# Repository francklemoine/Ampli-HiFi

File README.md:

# HiFi

This repository contains my amplifier and pre-amplifier schematics, program and housing.

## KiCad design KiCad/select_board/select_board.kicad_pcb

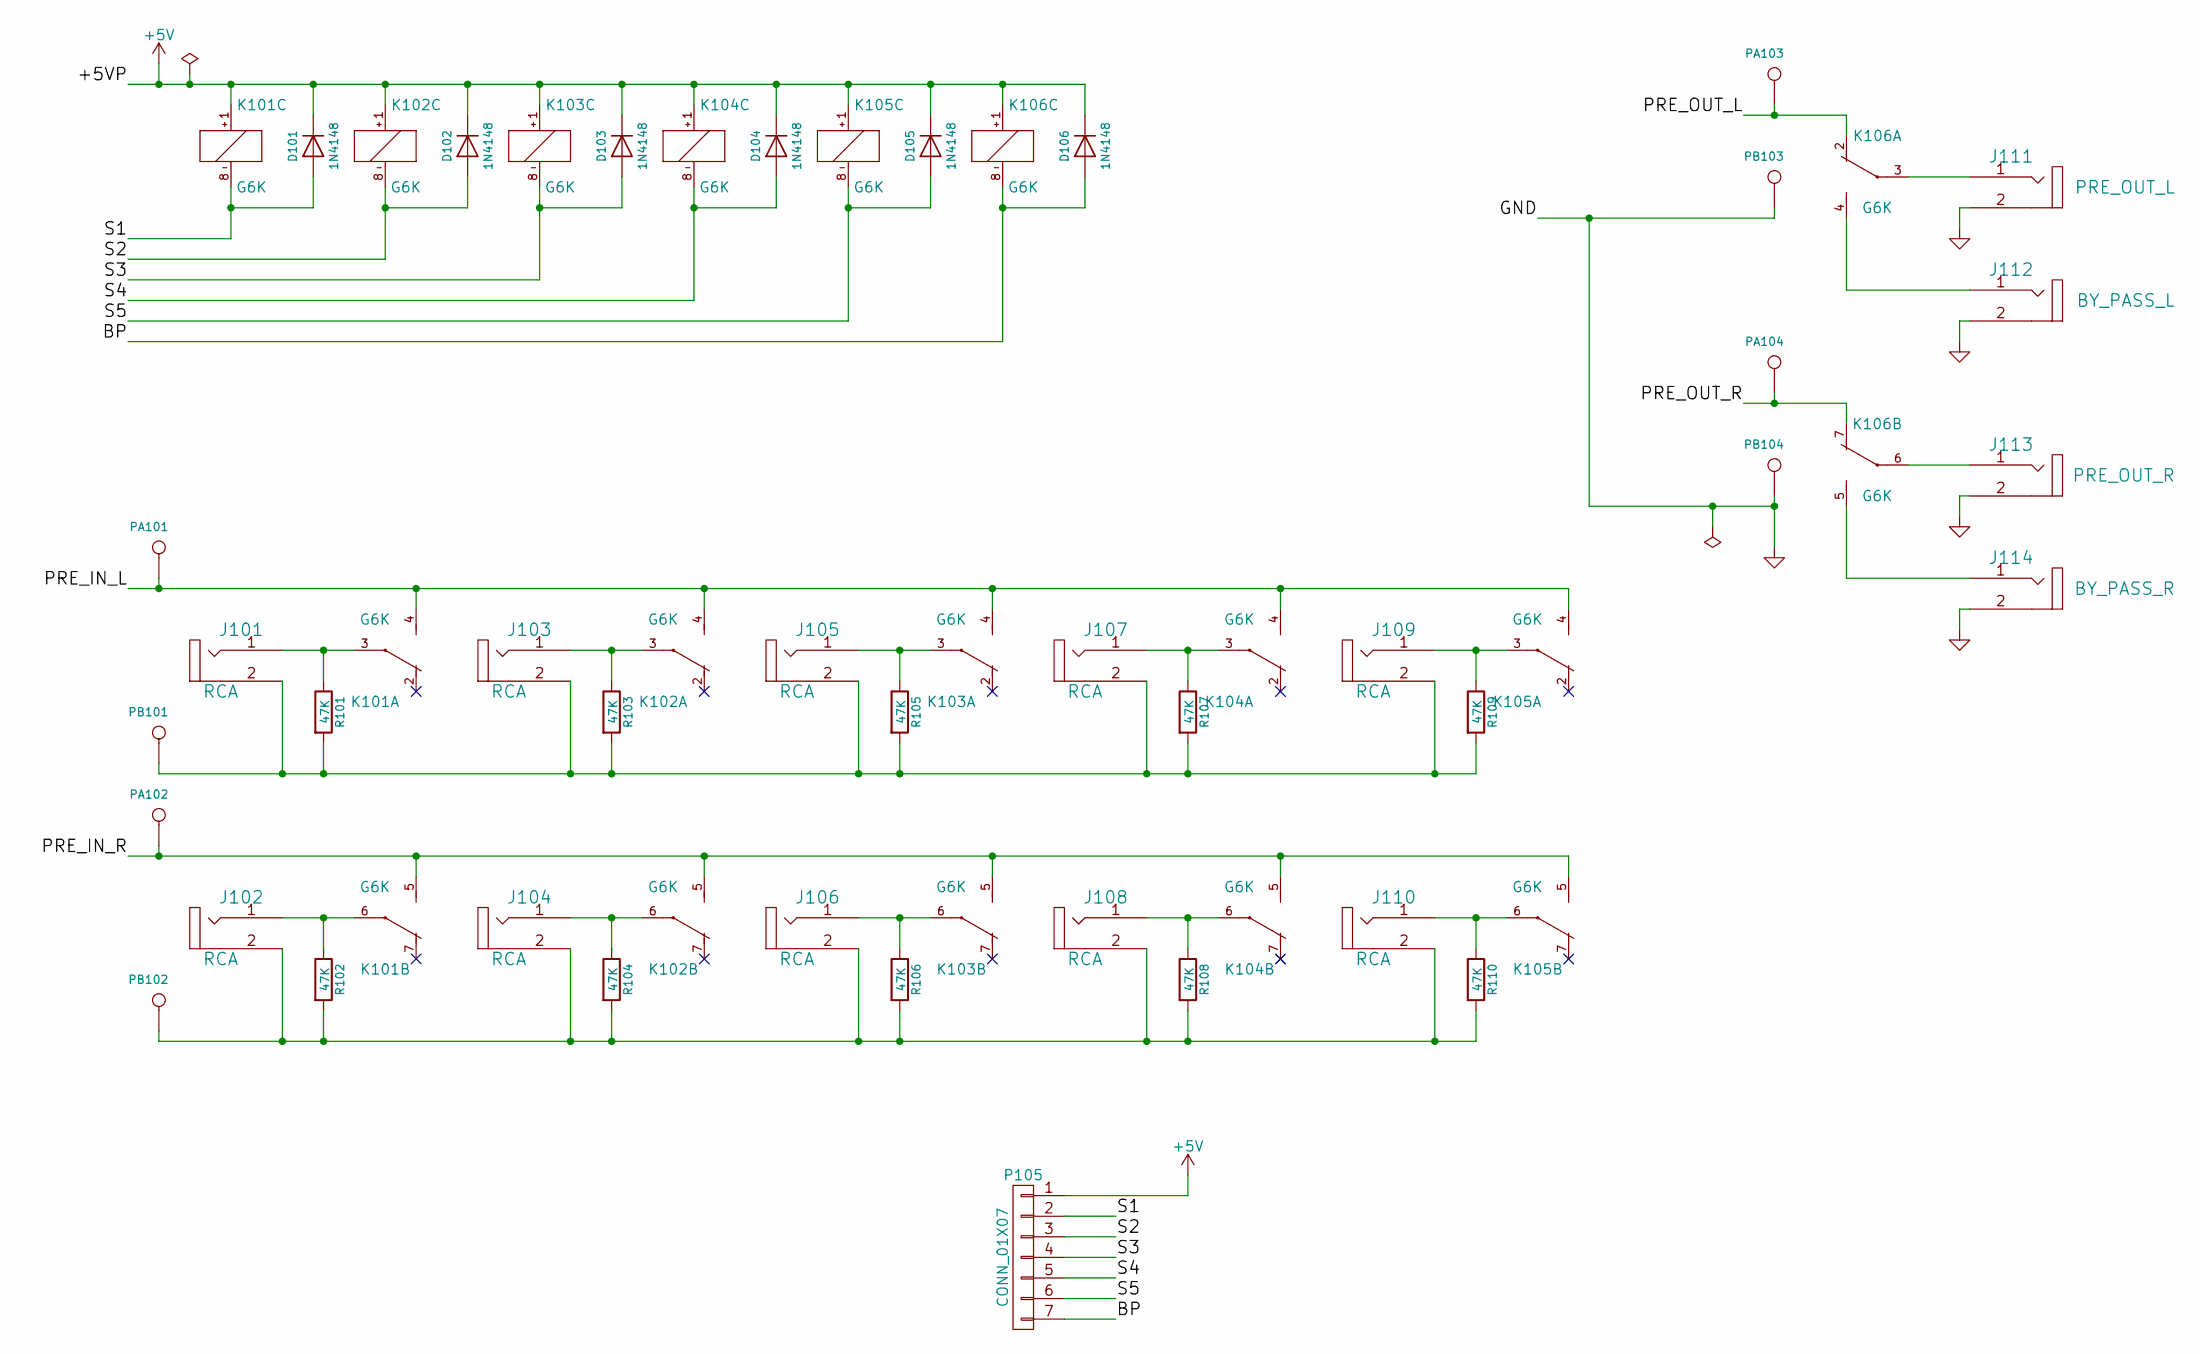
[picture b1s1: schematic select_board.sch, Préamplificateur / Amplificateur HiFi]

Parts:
D101, D102, D103, D104, D105, D106: 1N4148; D_DO-35_SOD27_P7.62mm_Horizontal
J101, J102, J103, J104, J105, J106, J107, J108, J109, J110: RCA; RCA_ELECAUDIO_ER107
J111: PRE_OUT_L; RCA_ELECAUDIO_ER107
J112: BY_PASS_L; RCA_ELECAUDIO_ER107
J113: PRE_OUT_R; RCA_ELECAUDIO_ER107
J114: BY_PASS_R; RCA_ELECAUDIO_ER107
K101, K102, K103, K104, K105, K106: G6K; Omron-G6K-2F-Y
P105: CONN_01X07; Pin_Header_Straight_1x07_Pitch2.54mm
PA101, PA102, PA103, PA104: CONN_1; 1Pin_d1.8mm_D3.4mm
PB101, PB102, PB103, PB104: CONN_1; 1Pin_d1.8mm_D3.4mm
R101, R102, R103, R104, R105, R106, R107, R108, R109, R110: 47K; R_1206

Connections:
+5V: D101.1 (K), D102.1 (K), D103.1 (K), D104.1 (K), D105.1 (K), D106.1 (K), K101.1 (+), K102.1 (+), K103.1 (+), K104.1 (+), K105.1 (+), K106.1 (+), P105.1
/BP: D106.2 (A), K106.8 (-), P105.7
/PRE_IN_L: K101.4 (S), K102.4 (S), K103.4 (S), K104.4 (S), K105.4 (S), PA101.1
/PRE_IN_R: K101.5 (S), K102.5 (S), K103.5 (S), K104.5 (S), K105.5 (S), PA102.1
/PRE_OUT_L: K106.2 (O), PA103.1
/PRE_OUT_R: K106.7 (O), PA104.1
/S1: D101.2 (A), K101.8 (-), P105.2
/S2: D102.2 (A), K102.8 (-), P105.3
/S3: D103.2 (A), K103.8 (-), P105.4
/S4: D104.2 (A), K104.8 (-), P105.5
/S5: D105.2 (A), K105.8 (-), P105.6
GND: J111.2 (S), J112.2 (S), J113.2 (S), J114.2 (S), PB103.1, PB104.1
unnamed: J101.1 (T), K101.3, R101.1
unnamed: J101.2 (S), J103.2 (S), J105.2 (S), J107.2 (S), J109.2 (S), PB101.1, R101.2, R103.2, R105.2, R107.2, R109.2
unnamed: J102.1 (T), K101.6, R102.1
unnamed: J102.2 (S), J104.2 (S), J106.2 (S), J108.2 (S), J110.2 (S), PB102.1, R102.2, R104.2, R106.2, R108.2, R110.2
unnamed: J103.1 (T), K102.3, R103.1
unnamed: J104.1 (T), K102.6, R104.1
unnamed: J105.1 (T), K103.3, R105.1
unnamed: J106.1 (T), K103.6, R106.1
unnamed: J107.1 (T), K104.3, R107.1
unnamed: J108.1 (T), K104.6, R108.1
unnamed: J109.1 (T), K105.3, R109.1
unnamed: J110.1 (T), K105.6, R110.1
unnamed: J111.1 (T), K106.3
unnamed: J112.1 (T), K106.4 (S)
unnamed: J113.1 (T), K106.6
unnamed: J114.1 (T), K106.5 (S)

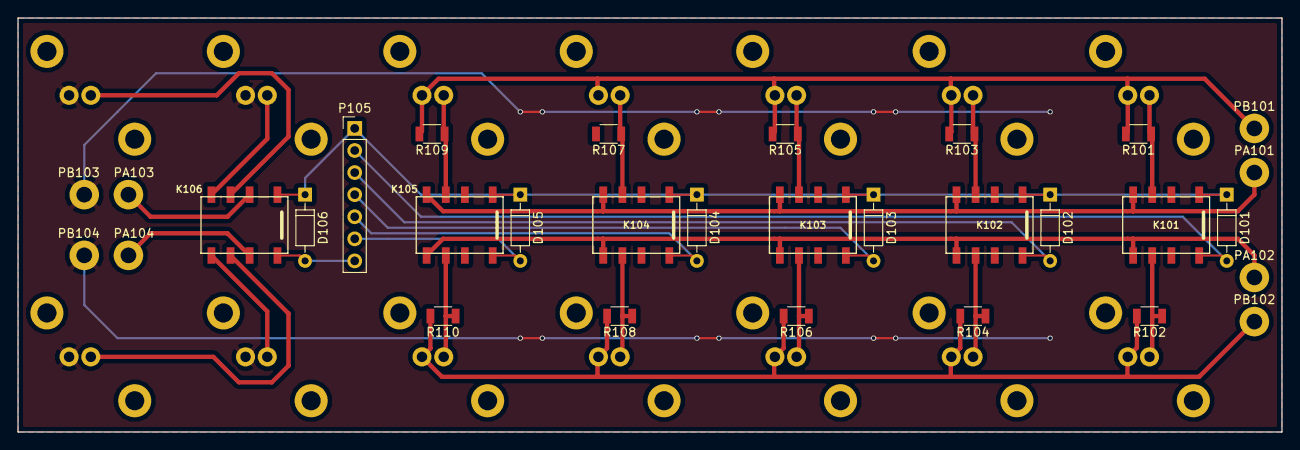
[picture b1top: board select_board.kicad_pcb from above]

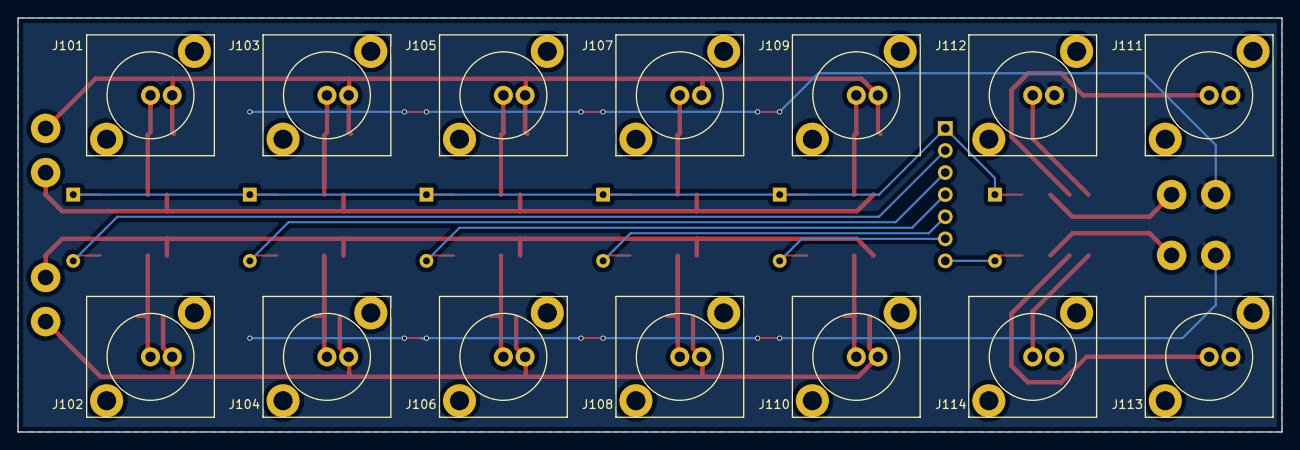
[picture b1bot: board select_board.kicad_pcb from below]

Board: 2 copper layers, 145.4 x 47.6 mm, 45 parts (14 on the bottom side), 28 nets.

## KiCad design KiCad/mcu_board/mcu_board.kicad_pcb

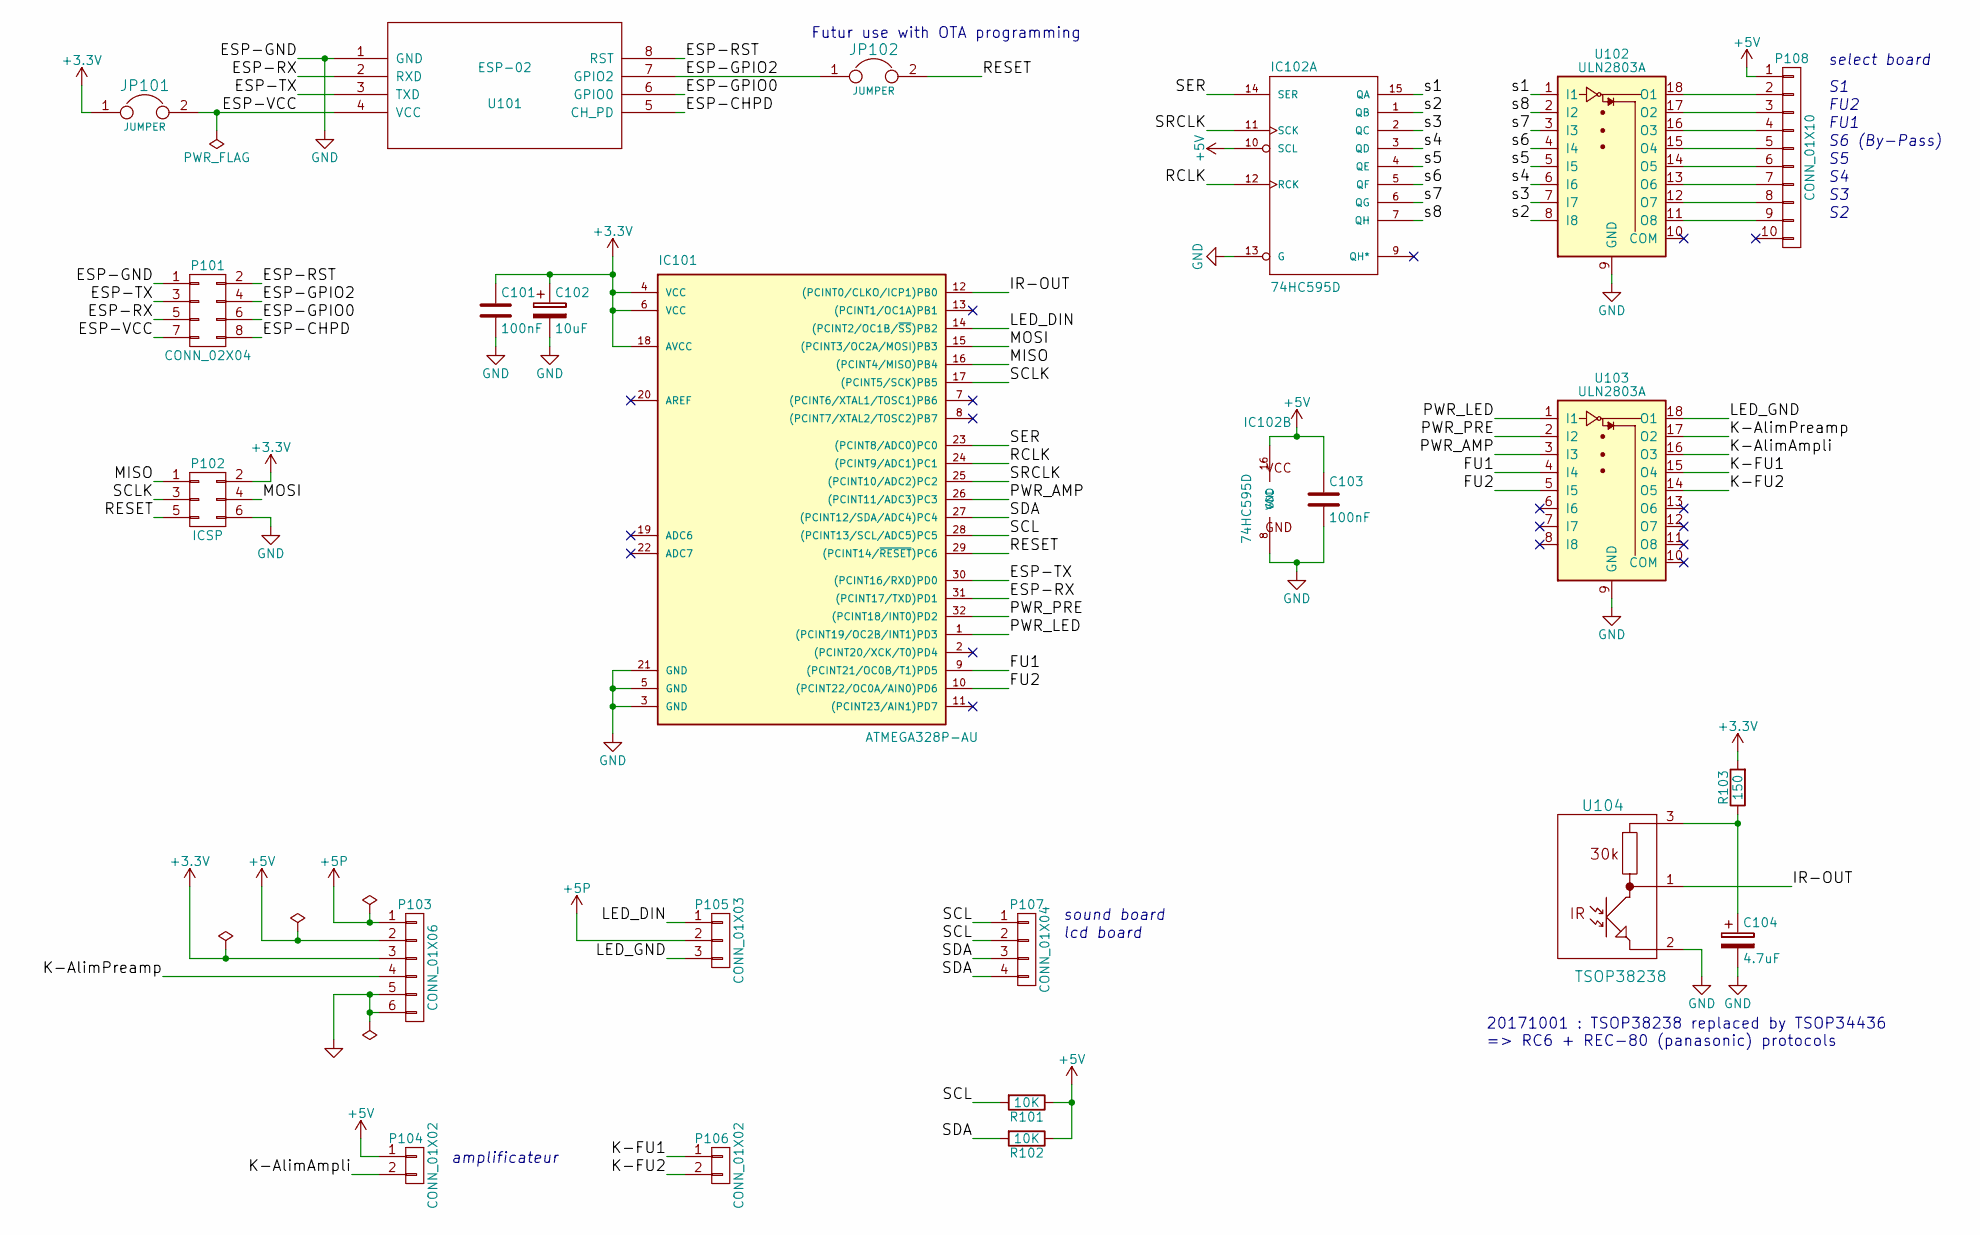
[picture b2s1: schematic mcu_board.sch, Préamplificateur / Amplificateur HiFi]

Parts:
C101, C103: 100nF; C_0603_HandSoldering
C102: 10uF; CP_Radial_D5.0mm_P2.50mm
C104: 4.7uF; CP_Radial_D5.0mm_P2.50mm
IC101: ATMEGA328P-AU; TQFP-32_7x7mm_Pitch0.8mm
IC102: 74HC595D; SO-16-N
JP101, JP102: JUMPER; Test_Point_2Pads
P101: CONN_02X04; Pin_Header_Straight_2x04_Pitch2.54mm
P102: ICSP; Pin_Header_Straight_2x03_Pitch2.54mm
P103: CONN_01X06; Pin_Header_Straight_1x06_Pitch2.54mm
P104, P106: CONN_01X02; Pin_Header_Straight_1x02_Pitch2.54mm
P105: CONN_01X03; Pin_Header_Straight_1x03_Pitch2.54mm
P107: CONN_01X04; Pin_Header_Straight_1x04_Pitch2.54mm
P108: CONN_01X10; Pin_Header_Straight_1x10_Pitch2.54mm
R101, R102: 10K; R_1206_HandSoldering
R103: 150; R_1206_HandSoldering
U101: ESP-02; ESP8266_ESP_02_SMD_Handsoldering
U102, U103: ULN2803A; SOIC-18W_7.5x11.6mm_Pitch1.27mm
U104: TSOP38238; TSOP382

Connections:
+3V3: C101.1, C102.1, IC101.4 (VCC), IC101.6 (VCC), IC101.18 (AVCC), JP101.1, P102.2, P103.3, R103.2
+5P: P103.1, P105.2
+5V: C103.1, IC102.10 (SCL), IC102.16 (VCC), P103.2, P104.1, P108.1, R101.1, R102.1
/ESP-CHPD: P101.8, U101.5 (CH_PD)
/ESP-GPIO0: P101.6, U101.6 (GPIO0)
/ESP-GPIO2: JP102.1, P101.4, U101.7 (GPIO2)
/ESP-RST: P101.2, U101.8 (RST)
/ESP-RX: IC101.31 ((PCINT17/TXD)PD1), P101.5, U101.2 (RXD)
/ESP-TX: IC101.30 ((PCINT16/RXD)PD0), P101.3, U101.3 (TXD)
/ESP-VCC: JP101.2, P101.7, U101.4 (VCC)
/FU1: IC101.9 ((PCINT21/OC0B/T1)PD5), U103.4 (I4)
/FU2: IC101.10 ((PCINT22/OC0A/AIN0)PD6), U103.5 (I5)
/IR-OUT: IC101.12 ((PCINT0/CLKO/ICP1)PB0), U104.1
/K-AlimAmpli: P104.2, U103.16 (O3)
/K-AlimPreamp: P103.4, U103.17 (O2)
/K-FU1: P106.1, U103.15 (O4)
/K-FU2: P106.2, U103.14 (O5)
/LED_DIN: IC101.14 ((PCINT2/OC1B/~SS~)PB2), P105.1
/LED_GND: P105.3, U103.18 (O1)
/MISO: IC101.16 ((PCINT4/MISO)PB4), P102.1
/MOSI: IC101.15 ((PCINT3/OC2A/MOSI)PB3), P102.4
/PWR_AMP: IC101.26 ((PCINT11/ADC3)PC3), U103.3 (I3)
/PWR_LED: IC101.1 ((PCINT19/OC2B/INT1)PD3), U103.1 (I1)
/PWR_PRE: IC101.32 ((PCINT18/INT0)PD2), U103.2 (I2)
/RCLK: IC101.24 ((PCINT9/ADC1)PC1), IC102.12 (RCK)
/RESET: IC101.29 ((PCINT14/~RESET~)PC6), JP102.2, P102.5
/SCL: IC101.28 ((PCINT13/SCL/ADC5)PC5), P107.1, P107.2, R101.2
/SCLK: IC101.17 ((PCINT5/SCK)PB5), P102.3
/SDA: IC101.27 ((PCINT12/SDA/ADC4)PC4), P107.3, P107.4, R102.2
/SER: IC101.23 ((PCINT8/ADC0)PC0), IC102.14 (SER)
/SRCLK: IC101.25 ((PCINT10/ADC2)PC2), IC102.11 (SCK)
/s1: IC102.15 (QA), U102.1 (I1)
/s2: IC102.1 (QB), U102.8 (I8)
/s3: IC102.2 (QC), U102.7 (I7)
/s4: IC102.3 (QD), U102.6 (I6)
/s5: IC102.4 (QE), U102.5 (I5)
/s6: IC102.5 (QF), U102.4 (I4)
/s7: IC102.6 (QG), U102.3 (I3)
/s8: IC102.7 (QH), U102.2 (I2)
GND: C101.2, C102.2, C103.2, C104.2, IC101.3 (GND), IC101.5 (GND), IC101.21 (GND), IC102.8 (GND), IC102.13 (G), P101.1, P102.6, P103.5, P103.6, U101.1 (GND), U102.9 (GND), U103.9 (GND), U104.2
unnamed: C104.1, R103.1, U104.3
unnamed: P108.2, U102.18 (O1)
unnamed: P108.3, U102.17 (O2)
unnamed: P108.4, U102.16 (O3)
unnamed: P108.5, U102.15 (O4)
unnamed: P108.6, U102.14 (O5)
unnamed: P108.7, U102.13 (O6)
unnamed: P108.8, U102.12 (O7)
unnamed: P108.9, U102.11 (O8)

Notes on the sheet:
select board
amplificateur
sound board
lcd board
S6 (By-Pass)
FU1
FU2
Futur use with OTA programming
20171001 : TSOP38238 replaced by TSOP34436 => RC6 + REC-80 (panasonic) protocols

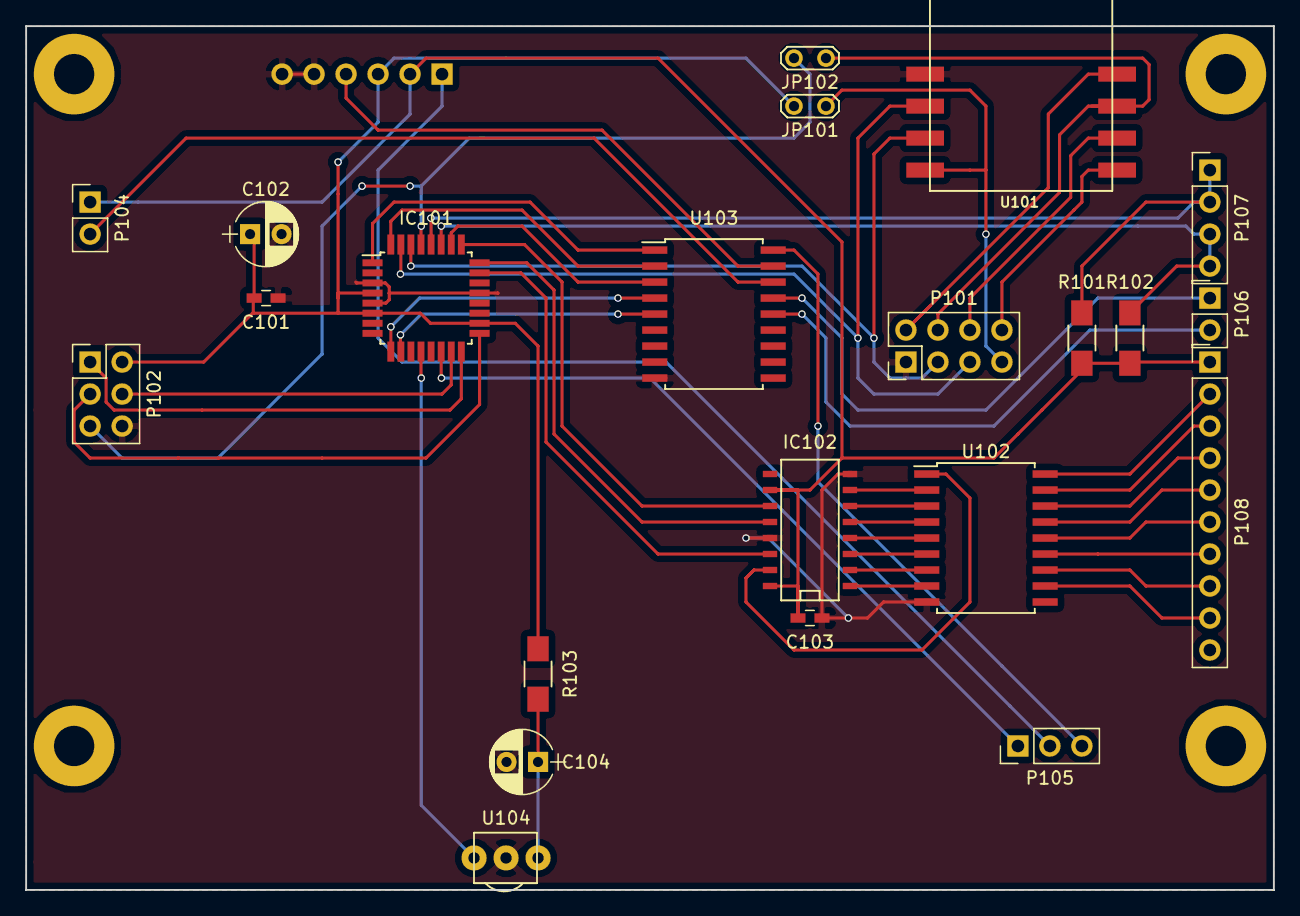
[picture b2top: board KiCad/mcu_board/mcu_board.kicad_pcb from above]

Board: 2 copper layers, 99.1 x 68.6 mm, 23 parts (1 on the bottom side), 49 nets.

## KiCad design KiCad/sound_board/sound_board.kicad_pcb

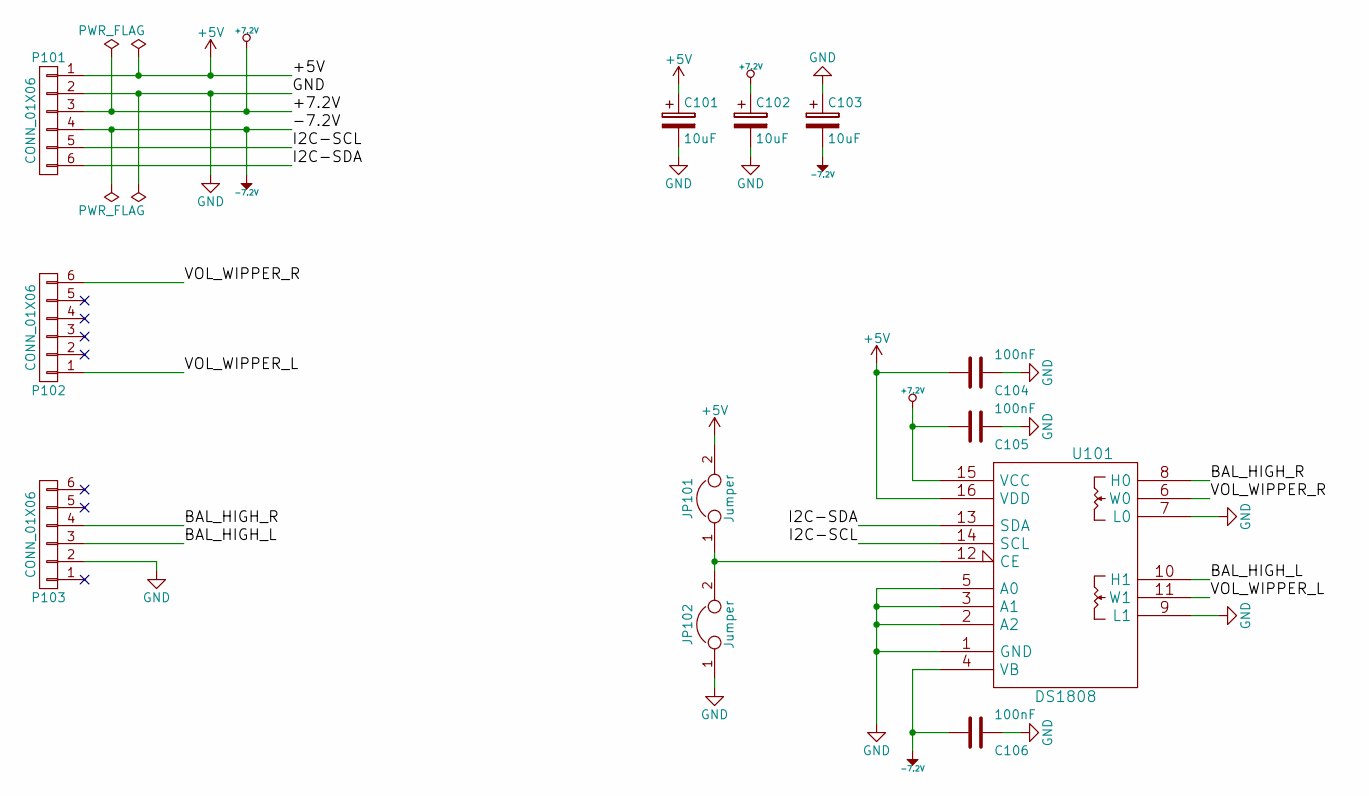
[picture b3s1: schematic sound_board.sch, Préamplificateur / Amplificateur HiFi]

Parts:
C101, C102, C103: 10uF; CP_Radial_D5.0mm_P2.50mm
C104, C105, C106: 100nF; C_0603_HandSoldering
JP101, JP102: Jumper; Test_Point_2Pads
P101, P102, P103: CONN_01X06; Pin_Header_Straight_1x06_Pitch2.54mm
U101: DS1808; SO-16-N

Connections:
+5V: C101.1, C104.2, JP101.2, P101.1, U101.16 (VDD)
+7.2V: C102.1, C105.2, P101.3, U101.15 (VCC)
-7.2V: C103.2, C106.2, P101.4, U101.4 (VB)
/BAL_HIGH_L: P103.3, U101.10 (H1)
/BAL_HIGH_R: P103.4, U101.8 (H0)
/I2C-SCL: P101.5, U101.14 (SCL)
/I2C-SDA: P101.6, U101.13 (SDA)
/VOL_WIPPER_L: P102.1, U101.11 (W1)
/VOL_WIPPER_R: P102.6, U101.6 (W0)
GND: C101.2, C102.2, C103.1, C104.1, C105.1, C106.1, JP102.1, P101.2, P103.2, U101.1 (GND), U101.2 (A2), U101.3 (A1), U101.5 (A0), U101.7 (L0), U101.9 (L1)
unnamed: JP101.1, JP102.2, U101.12 (CE)

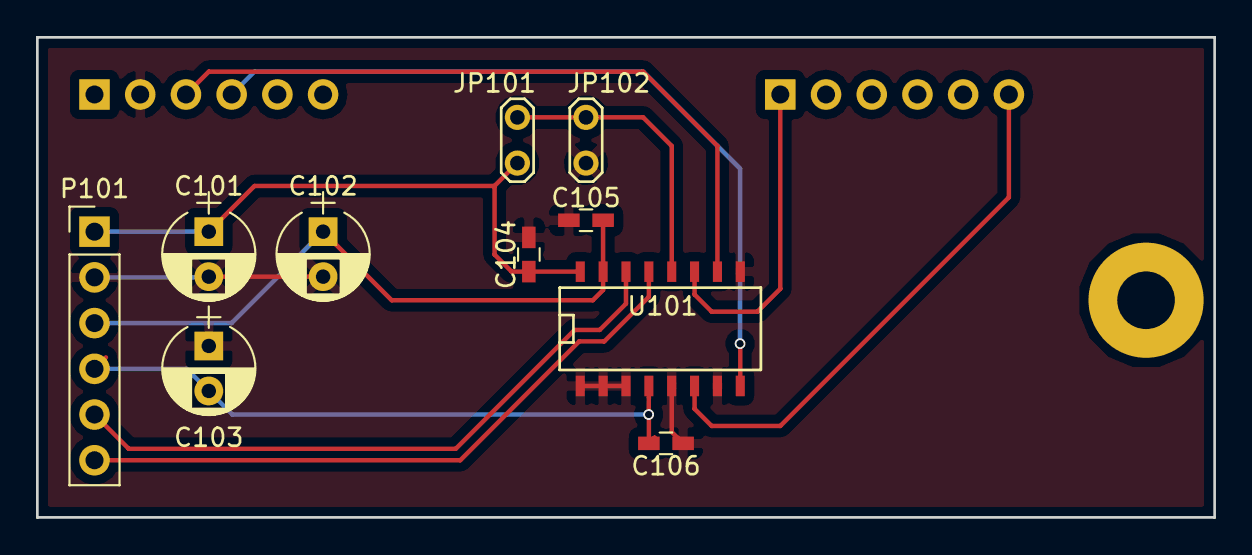
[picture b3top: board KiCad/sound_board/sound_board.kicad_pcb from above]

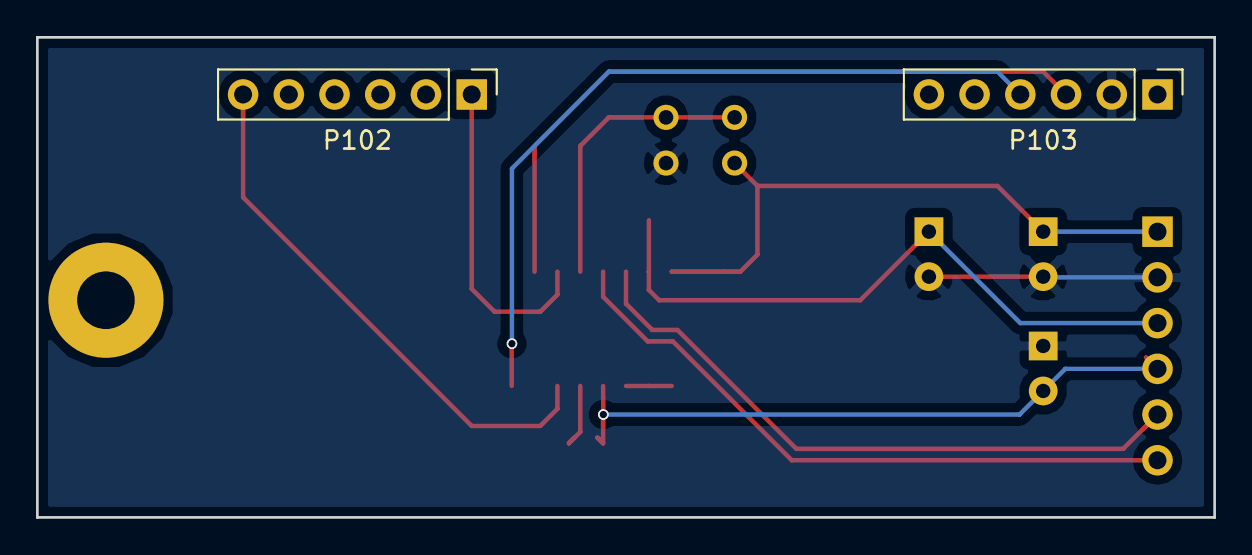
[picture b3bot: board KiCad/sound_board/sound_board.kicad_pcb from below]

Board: 2 copper layers, 65.4 x 26.7 mm, 12 parts (2 on the bottom side), 11 nets.

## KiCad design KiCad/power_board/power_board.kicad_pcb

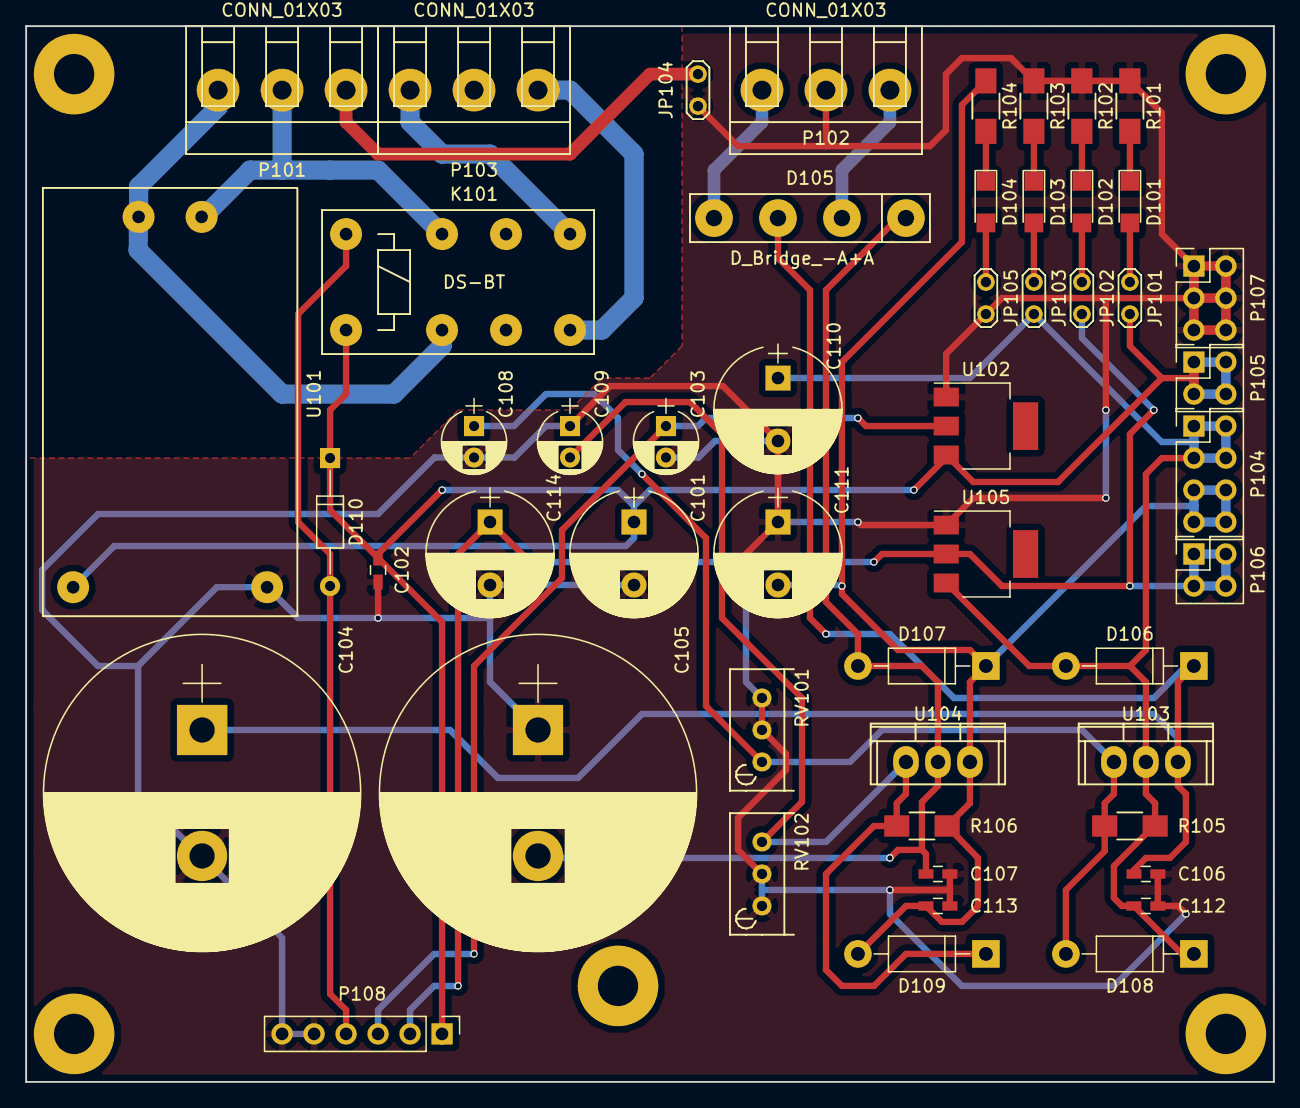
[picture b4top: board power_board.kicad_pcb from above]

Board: 2 copper layers, 99.1 x 83.8 mm, 51 parts (0 on the bottom side), 26 nets.

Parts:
C101, C110, C111, C114: 100uF; CP_Radial_D10.0mm_P5.00mm
C102, C106, C107, C112, C113: 100nF; C_0603_HandSoldering
C103, C108, C109: 10uF; CP_Radial_D5.0mm_P2.50mm
C104, C105: 10000uF; CP_Radial_D25.0mm_P10.00mm_SnapIn
D101, D102, D103, D104: LED; LED_1206
D105: D_Bridge_-A+A; Bridge
D106, D107, D108, D109: 1N4007; D_DO-41_SOD81_P10.16mm_Horizontal
D110: 1N4148; D_DO-35_SOD27_P10.16mm_Horizontal
JP101, JP102, JP103, JP104, JP105: JUMPER; Test_Point_2Pads
K101: DS-BT; Relay_DS-BT_Nais
P101, P102, P103: CONN_01X03; CONN_AK350_03_5.08
P104: CONN_02X04; Pin_Header_Straight_2x04_Pitch2.54mm
P105, P106: CONN_02X02; Pin_Header_Straight_2x02_Pitch2.54mm
P107: CONN_02X03; Pin_Header_Straight_2x03_Pitch2.54mm
P108: CONN_01X06; Pin_Header_Straight_1x06_Pitch2.54mm
R101, R102: 330; R_1206_HandSoldering
R103, R104: 560; R_1206_HandSoldering
R105, R106: 220; R_1206_HandSoldering
RV101, RV102: 2.2K; Potentiometer_Bourns_3296W_3-8Zoll_Inline_ScrewUp
U101: HLK-PM01
U102: AMS117; SOT-223
U103: LM317AT/NOPB; TO-220
U104: LM337T/NOPB; TO-220
U105: LT1117; SOT-223

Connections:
+3V3: C103.1, P108.3, U102.2
+5P: C101.1, C102.1, D110.1, JP101.2, K101.1, P105.1, P105.2, P105.3, P105.4, P108.1, U101.4, U102.3
+5V: C114.1, JP102.2, P106.1, P106.2, P106.3, P106.4, P108.2, U105.2
+7.2V: C110.1, C112.1, D106.2, D108.1, JP103.2, P104.1, P104.2, P104.3, P104.4, R105.1, U103.2, U105.3
-7.2V: C111.2, C113.2, D107.1, D109.2, P104.5, P104.6, P104.7, P104.8, R104.2, R106.2, U104.3
/K-AlimPreamp: D110.2, K101.16, P108.4
/Neutre: K101.13, P101.2, U101.1
/Phase: K101.4, P101.3, U101.2
/Terre: JP104.1, P101.1
/Torique_0_Blue: K101.9, P103.3
/Torique_0_Orange: D105.2, P102.1
/Torique_9_Red: D105.4, P102.3
/Torique_115_Brown: K101.8, P103.1
GND: C101.2, C102.2, C103.2, C104.2, C105.1, C106.2, C107.1, C108.2, C109.1, C110.2, C111.1, C112.2, C113.1, C114.2, JP104.2, JP105.2, P102.2, P107.1, P107.2, P107.3, P107.4, P107.5, P107.6, P108.5, P108.6, R101.2, R102.2, R103.2, RV101.2, RV101.3, RV102.1, RV102.2, U101.3, U102.1, U105.1
unnamed: C104.1, C106.1, D105.3, D106.1, U103.3
unnamed: C105.2, C107.2, D105.1, D107.2, U104.2
unnamed: C108.1, D108.2, R105.2, RV101.1, U103.1
unnamed: C109.2, D109.1, R106.1, RV102.3, U104.1
unnamed: D101.1, R101.1
unnamed: D101.2, JP101.1
unnamed: D102.1, R102.1
unnamed: D102.2, JP102.1
unnamed: D103.1, R103.1
unnamed: D103.2, JP103.1
unnamed: D104.1, R104.1
unnamed: D104.2, JP105.1

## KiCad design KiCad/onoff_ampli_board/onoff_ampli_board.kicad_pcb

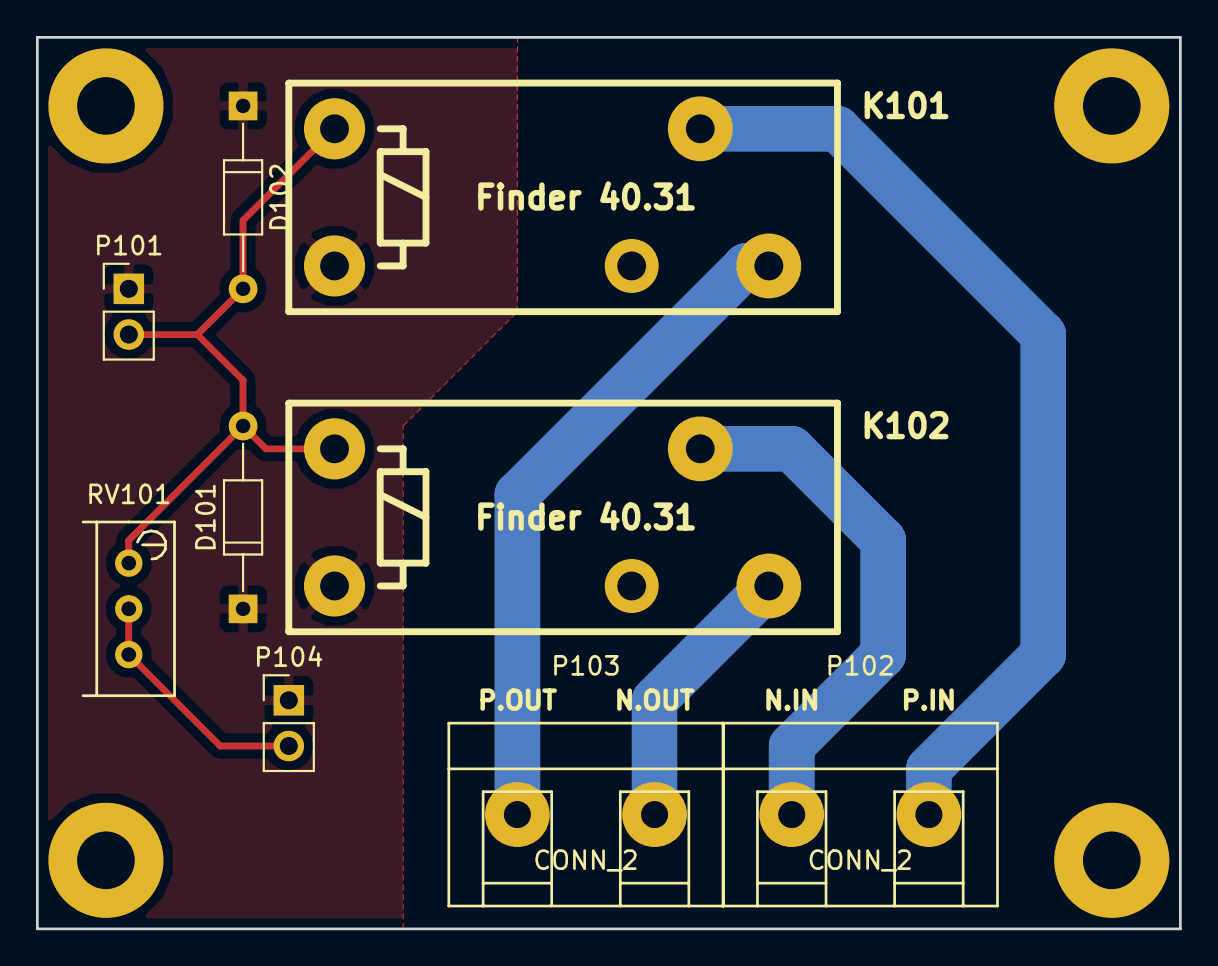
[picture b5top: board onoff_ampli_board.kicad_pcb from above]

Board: 2 copper layers, 63.5 x 49.5 mm, 9 parts (0 on the bottom side), 7 nets.

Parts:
D101, D102: 1N4148; D_DO-35_SOD27_P10.16mm_Horizontal
K101, K102: Finder 40.31; Relay_40.31_Finder
P101, P104: CONN_2; Pin_Header_Straight_1x02_Pitch2.54mm
P102, P103: CONN_2; CONN_AK350_02_7.62
RV101: 4.7K; Potentiometer_Bourns_3296W_3-8Zoll_Inline_ScrewUp

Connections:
+5V: D101.1, D102.1, K101.A1, K102.A1, P101.1, P104.1
/K: D101.2, D102.2, K101.A2, K102.A2, P101.2, RV101.1
/N.IN: K102.11, P102.1
/N.LED_K: P104.2, RV101.2, RV101.3
/N.OUT: K102.14, P103.2
/P.IN: K101.11, P102.2
/P.OUT: K101.14, P103.1

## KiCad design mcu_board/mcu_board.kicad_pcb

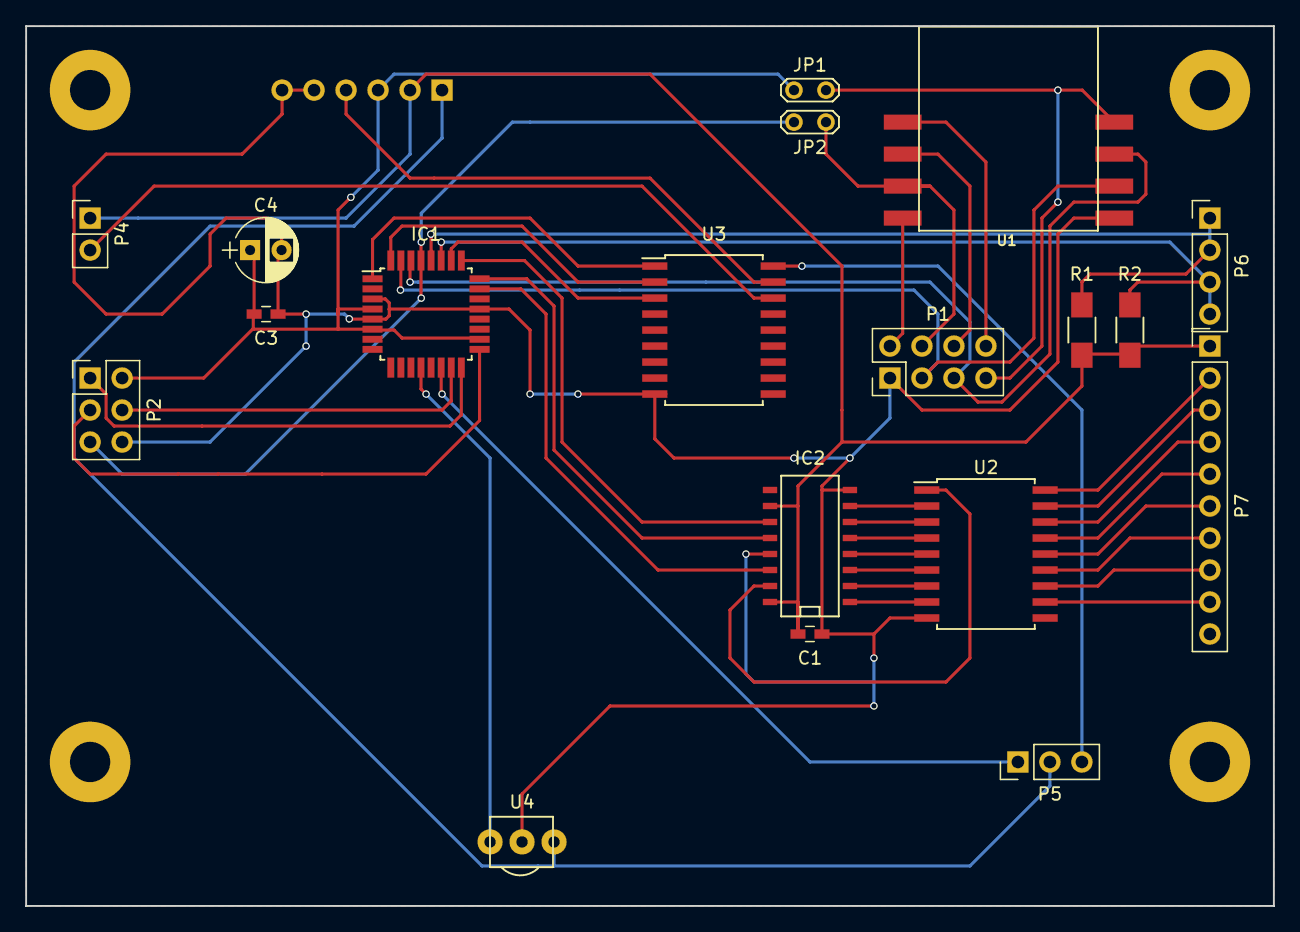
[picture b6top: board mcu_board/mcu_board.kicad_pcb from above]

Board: 2 copper layers, 99.1 x 69.8 mm, 20 parts (1 on the bottom side), 44 nets.

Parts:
C1, C3: 100nF; C_0603_HandSoldering
C4: 10uF; CP_Radial_D5.0mm_P2.50mm
IC1: ATMEGA328P-AU; TQFP-32_7x7mm_Pitch0.8mm
IC2: 74HC595D; SO-16-N
JP1, JP2: JUMPER; Test_Point_2Pads
P1: CONN_02X04; Pin_Header_Straight_2x04_Pitch2.54mm
P2: ICSP; Pin_Header_Straight_2x03_Pitch2.54mm
P3: CONN_01X06; Pin_Header_Straight_1x06_Pitch2.54mm
P4: CONN_01X02; Pin_Header_Straight_1x02_Pitch2.54mm
P5: CONN_01X03; Pin_Header_Straight_1x03_Pitch2.54mm
P6: CONN_01X04; Pin_Header_Straight_1x04_Pitch2.54mm
P7: CONN_01X10; Pin_Header_Straight_1x10_Pitch2.54mm
R1, R2: 10K; R_1206_HandSoldering
U1: ESP-02; ESP_02_SMD_Handsoldering
U2, U3: ULN2803A; SOIC-18W_7.5x11.6mm_Pitch1.27mm
U4: TSOP38238; TSOP382

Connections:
+3V3: C3.1, C4.1, IC1.4, IC1.6, IC1.18, JP1.1, P2.2, P3.3
+5P: P3.1, P5.2, U4.3
+5V: C1.1, IC2.10, IC2.16, P3.2, P4.1, P7.1, R1.1, R2.1
/ESP-GPIO0: P1.6, U1.6
/ESP-GPIO2: JP2.1, P1.4, U1.7
/ESP-GPIO15: P1.8, U1.5
/ESP-RST: P1.2, U1.8
/ESP-RX: IC1.31, P1.3, U1.2
/ESP-TX: IC1.30, P1.5, U1.3
/ESP-VCC: JP1.2, P1.7, U1.4
/IR-OUT: IC1.12, U4.1
/K-AlimAmpli: P4.2, U3.16
/K-AlimPreamp: P3.4, U3.17
/LED_DIN: IC1.14, P5.1
/LED_GND: P5.3, U3.18
/MISO: IC1.16, P2.1
/MOSI: IC1.15, P2.4
/PWR_AMP: IC1.26, U3.3
/PWR_LED: IC1.1, U3.1
/PWR_PRE: IC1.32, U3.2
/RCLK: IC1.24, IC2.12
/RESET: IC1.29, JP2.2, P2.5
/SCL: IC1.28, P6.1, P6.2, R1.2
/SCLK: IC1.17, P2.3
/SDA: IC1.27, P6.3, P6.4, R2.2
/SER: IC1.23, IC2.14
/SRCLK: IC1.25, IC2.11
/hp: IC2.7, U2.2
/s1: IC2.15, U2.1
/s2: IC2.1, U2.8
/s3: IC2.2, U2.7
/s4: IC2.3, U2.6
/s5: IC2.4, U2.5
/s6: IC2.5, U2.4
/s7: IC2.6, U2.3
GND: C1.2, C3.2, C4.2, IC1.3, IC1.5, IC1.21, IC2.8, IC2.13, P1.1, P2.6, P3.5, P3.6, U1.1, U2.9, U3.9, U4.2
unnamed: P7.2, U2.18
unnamed: P7.3, U2.17
unnamed: P7.4, U2.16
unnamed: P7.5, U2.15
unnamed: P7.6, U2.14
unnamed: P7.7, U2.13
unnamed: P7.8, U2.12
unnamed: P7.9, U2.11
